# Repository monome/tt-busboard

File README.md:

# teletype busboard

provides 12 ii headers and additional pull-up to support larger ii networks.

## bom

see http://digikey.com

* (1) header, female, 2x3 [S7071-ND](https://www.digikey.com/products/en?keywords=S7071-ND)
* (12) header, male, 2x3 [609-3218-ND](https://www.digikey.com/products/en?keywords=609-3218-ND)
* (1) 3v3 reg [AZ1117CH-3.3TRG1DICT-ND](https://www.digikey.com/products/en?keywords=Z1117CH-3.3TRG1DICT-ND)
* (1) header, female, 2x5 [S6105-ND](https://www.digikey.com/products/en?keywords=S6105-ND)
* (2) resistor 1206 2.2k [P2.20KFCT-ND](https://www.digikey.com/products/en?keywords=P2.20KFCT-ND)
* (1) header, male, shrouded, 2x5 [ED1543-ND](https://www.digikey.com/products/en?keywords=ED1543-ND)

pcb via oshpark: https://oshpark.com/shared_projects/kg4mZSCg 

## guide

* full kit contents:

* solder the SMD pads first, one for each part. use tweezers to place the part while heating the soldered pad with the iron. pull the iron away while holding the part, let the solder cool.

* then solder the other remaining legs of the parts:

* should look more or less like this:

* insert the 12 headers as shown and then solder the other side. may require a trick to flip it without having them fall out-- try a bit of cardboard to hold it all together while flipping:

* insert female headers as shown then solder:

* insert the power header and solder. *IMPORTANT* make sure the key cutout is towards the outside of the board:

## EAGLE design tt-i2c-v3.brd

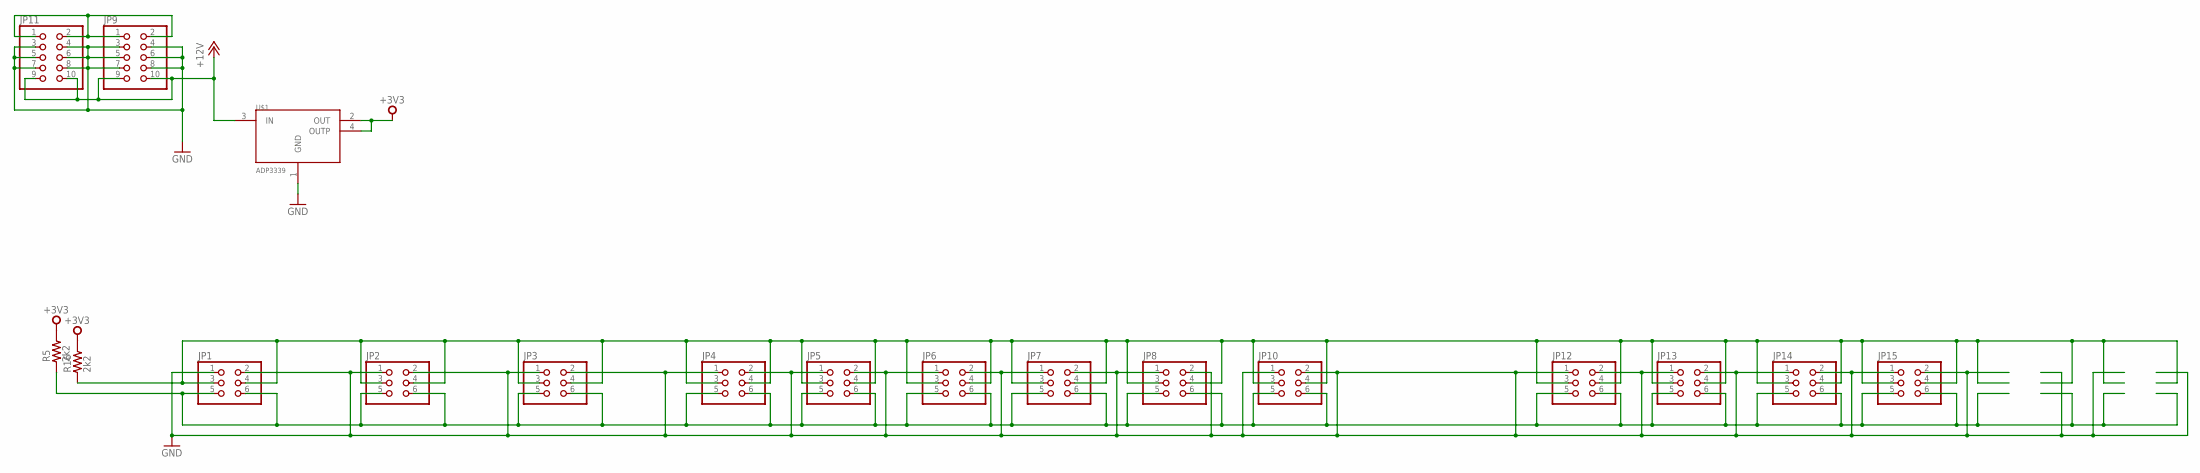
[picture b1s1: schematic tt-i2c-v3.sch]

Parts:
JP1, JP2, JP3, JP4, JP5, JP6, JP7, JP8, JP10, JP12, JP13, JP14, JP15: PINHD-2X3; 2X03
JP9, JP11: PINHD-2X5; 2X05
R5, R16: 2k2; R1206
U$1: ADP3339; SOT223

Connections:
+3V3: R5.2, R16.2, U$1.2 (OUT), U$1.4 (OUTP)
+12V: JP9.9, JP9.10, JP11.9, JP11.10, U$1.3 (IN)
GND: JP1.1, JP1.2, JP2.1, JP2.2, JP3.1, JP3.2, JP4.1, JP4.2, JP5.1, JP5.2, JP6.1, JP6.2, JP7.1, JP7.2, JP8.1, JP8.2, JP9.3, JP9.4, JP9.5, JP9.6, JP9.7, JP9.8, JP10.1, JP10.2, JP11.3, JP11.4, JP11.5, JP11.6, JP11.7, JP11.8, JP12.1, JP12.2, JP13.1, JP13.2, JP14.1, JP14.2, JP15.1, JP15.2, U$1.1 (GND)
unnamed: JP1.3, JP1.4, JP2.3, JP2.4, JP3.3, JP3.4, JP4.3, JP4.4, JP5.3, JP5.4, JP6.3, JP6.4, JP7.3, JP7.4, JP8.3, JP8.4, JP10.3, JP10.4, JP12.3, JP12.4, JP13.3, JP13.4, JP14.3, JP14.4, JP15.3, JP15.4, R16.1
unnamed: JP1.5, JP1.6, JP2.5, JP2.6, JP3.5, JP3.6, JP4.5, JP4.6, JP5.5, JP5.6, JP6.5, JP6.6, JP7.5, JP7.6, JP8.5, JP8.6, JP10.5, JP10.6, JP12.5, JP12.6, JP13.5, JP13.6, JP14.5, JP14.6, JP15.5, JP15.6, R5.1
unnamed: JP9.1, JP9.2, JP11.1, JP11.2

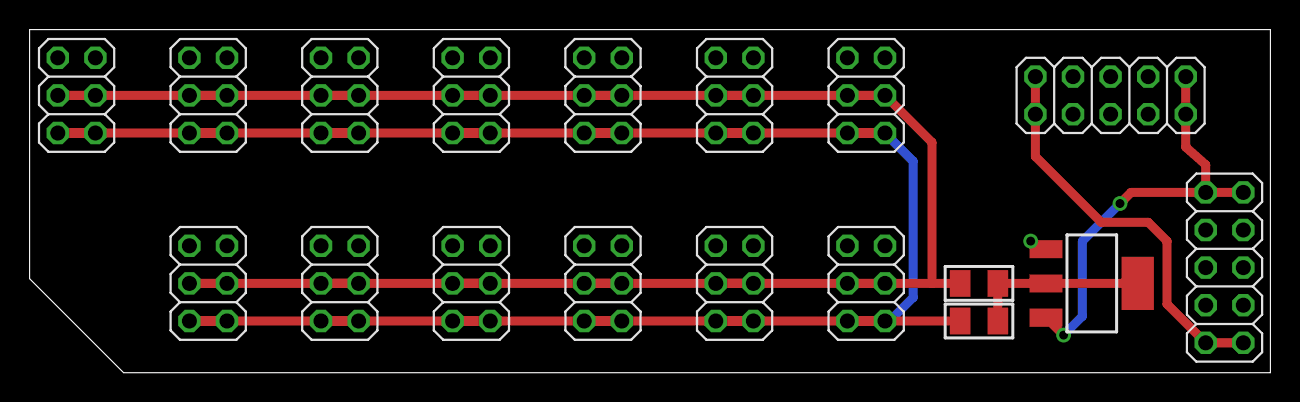
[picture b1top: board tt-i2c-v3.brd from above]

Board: 2 copper layers, 83.8 x 23.2 mm, 18 parts (0 on the bottom side), 6 nets.

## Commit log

2017-10-09 init
2017-10-09 bullet
2017-10-09 brd/sch
2017-10-09 pics
2017-10-09 typo
2017-10-09 directions
2018-06-18 Correct 2x3 male, 2x5 female; add resistor part#; add links to all parts.
